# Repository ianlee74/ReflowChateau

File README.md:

# Reflow Chateau
The Reflow Chateau is a set of mods created by Will Floyd-Jones to convert a toaster oven to a reflow oven.  These are my mods/improvements to his original design.

The original Reflow Chateau project can be found here:
http://www.willfj.com/reflow-chateau/

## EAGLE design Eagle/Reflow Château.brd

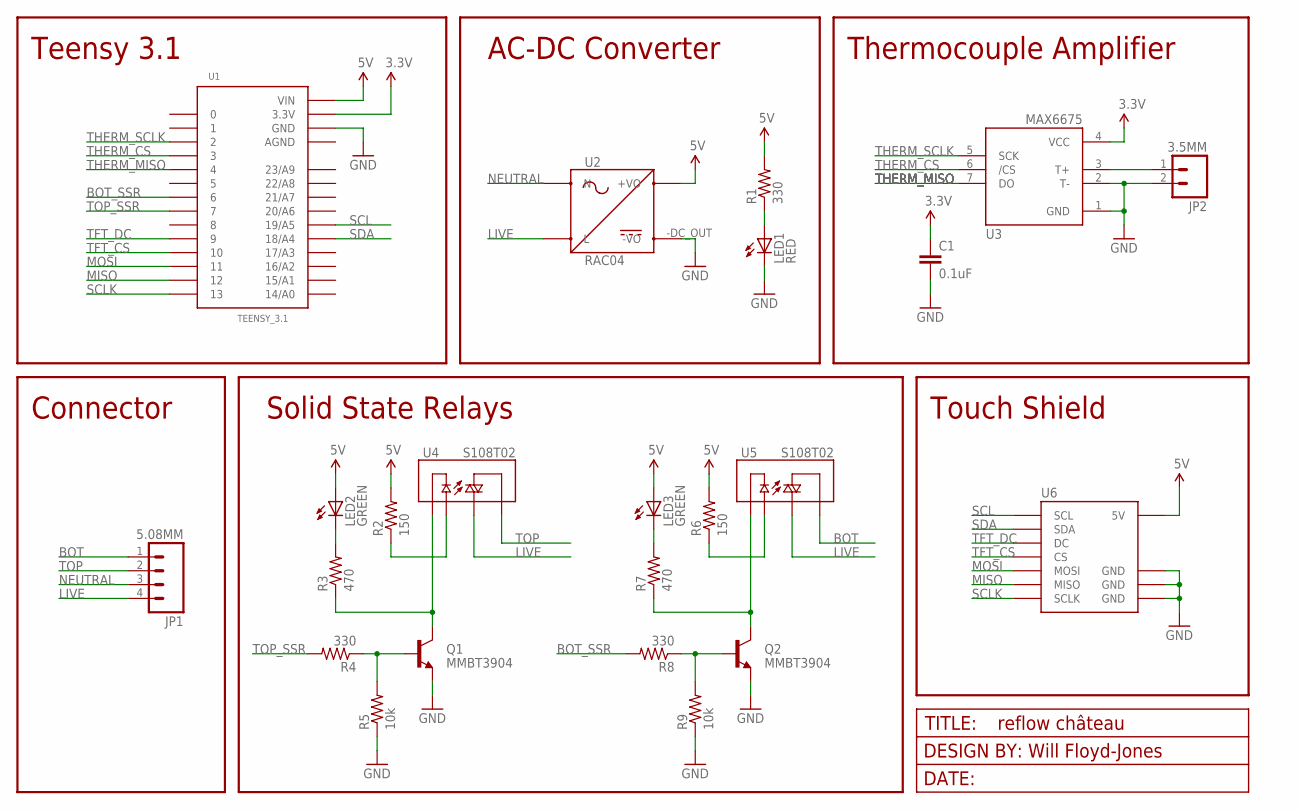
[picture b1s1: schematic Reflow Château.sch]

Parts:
C1: 0.1uF; 0603-CAP
JP1: 5.08MM; SCREWTERMINAL-5.08MM-4
JP2: 3.5MM; SCREWTERMINAL-3.5MM-2_LOCK
LED1: RED; LED-1206
LED2, LED3: GREEN; LED-1206
Q1, Q2: MMBT3904; SOT23-3
R1, R4, R8: 330; 0603-RES
R2, R6: 150; 0603-RES
R3, R7: 470; 0603-RES
R5, R9: 10k; 0603-RES
U1: TEENSY_3.1
U2: RAC04
U3: MAX6675; SO08
U4, U5: S108T02; RELAY-S108T02
U6: CAPACITIVE_TOUCH
U$9: FRAME; F-J_LOGO

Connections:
3.3V: C1.1, U1.3.3V, U3.4 (VCC)
5V: LED2.A, LED3.A, R1.2, R2.2, R6.2, U1.VIN, U2.+DC_OUT (+VO), U6.5V
AGND: U1.AGND
BOT: JP1.1, U5.1 (T1)
BOT_SSR: R8.2, U1.6
COIL: Q1.3 (C), R3.1, U4.4 (-)
COIL1: Q2.3 (C), R7.1, U5.4 (-)
GND: C1.2, JP2.2, LED1.C, Q1.2 (E), Q2.2 (E), R5.1, R9.1, U1.GND, U2.-DC_OUT (-VO), U3.1 (GND), U3.2 (T-), U6.GND, U6.GND@1 (GND), U6.GND@2 (GND)
LIVE: JP1.4, U2.LIVE (L), U4.2 (T2), U5.2 (T2)
MISO: U1.12, U6.D12 (MISO)
MOSI: U1.11, U6.D11 (MOSI)
unnamed: JP2.1, U3.3 (T+)
unnamed: R2.1, U4.3 (+)
unnamed: Q2.1 (B), R8.1, R9.2
unnamed: Q1.1 (B), R4.1, R5.2
unnamed: LED1.A, R1.1
unnamed: LED3.C, R7.2
unnamed: LED2.C, R3.2
unnamed: R6.1, U5.3 (+)
NEUTRAL: JP1.3, U2.NEUTRAL (N)
SCL: U1.19/A5, U6.SCL
SCLK: U1.13, U6.D13 (SCLK)
SDA: U1.18/A4, U6.SDA
TFT_CS: U1.10, U6.D10 (CS)
TFT_DC: U1.9, U6.D9 (DC)
THERM_CS: U1.3, U3.6 (/CS)
THERM_MISO: U1.4, U3.7 (DO)
THERM_SCLK: U1.2, U3.5 (SCK)
TOP: JP1.2, U4.1 (T1)
TOP_SSR: R4.2, U1.7

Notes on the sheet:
AC-DC Converter
Thermocouple Amplifier
Solid State Relays
Touch Shield
Connector
Teensy 3.1

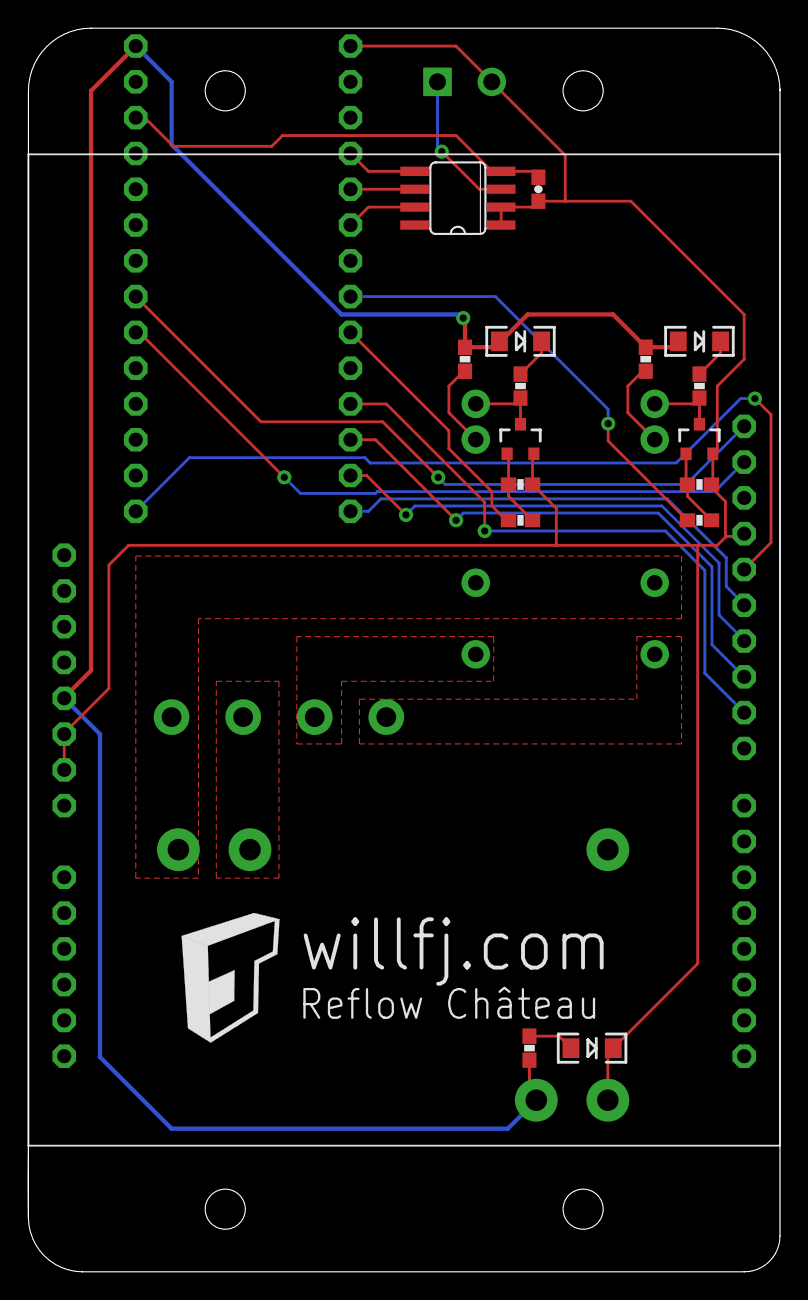
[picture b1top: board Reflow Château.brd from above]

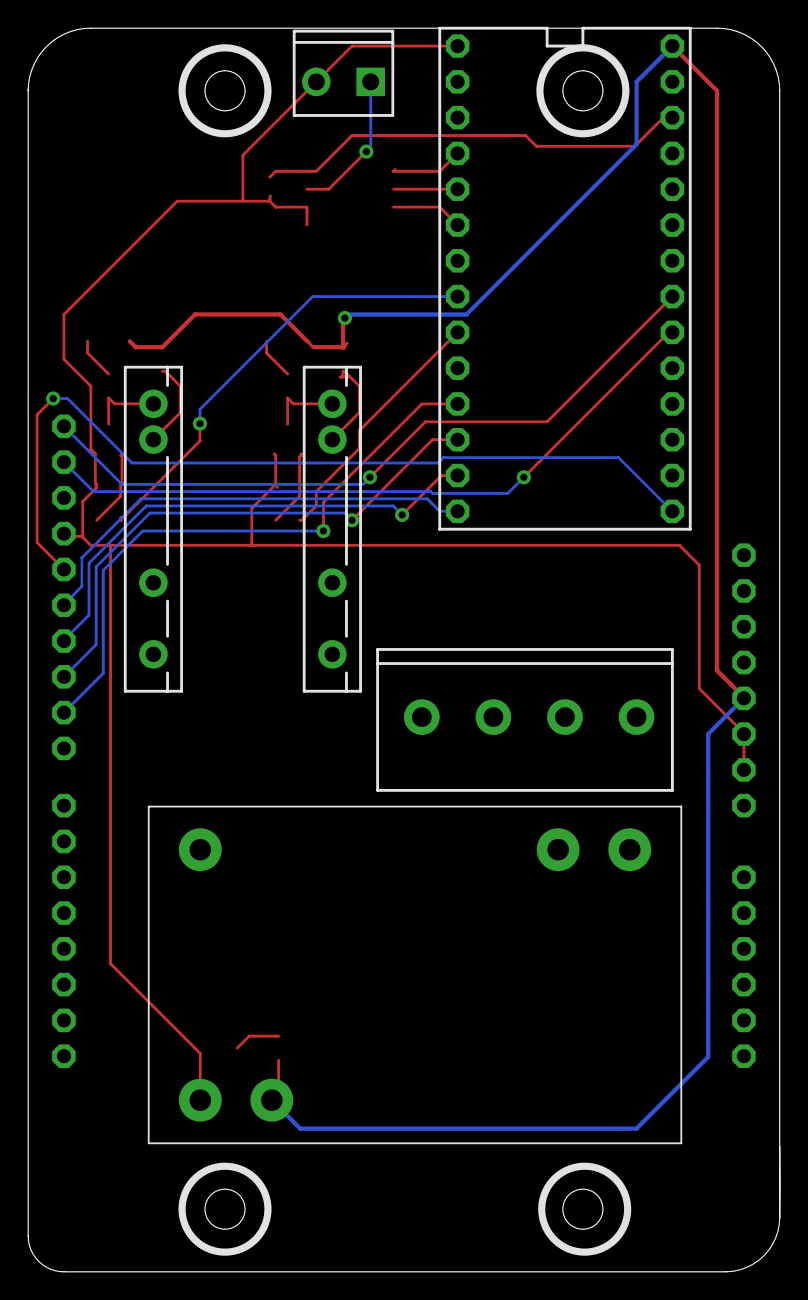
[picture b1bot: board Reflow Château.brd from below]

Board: 2 copper layers, 53.4 x 88.3 mm, 24 parts (6 on the bottom side), 29 nets.

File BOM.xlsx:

Device | Package | Part Number(s) | Quantity | Vendor | Vendor Pin | Unit Price | Ext Price
MAX6675 | SO08 | U3 | 1 | Digikey | MAX6675ISA+TCT-ND | 14.33 | 14.33
S108T02 SSR | 4-SIP | U4, U5 | 2 | Digikey | 425-2396-5-ND | 5.0999999999999996 | 10.199999999999999
Screw Terminal | 3.50 mm pitch | JP2 | 1 | Digikey | ED1514-ND | 0.68 | 0.68
Screw Terminal | 5.08 mm pitch | JP1 | 1 | Digikey | 281-1437-ND | 2.04 | 2.04
0.8 A, 5V AC-DC Converter | Through hole | U2 | 1 | Digikey | 945-2164-5-ND | 15.02 | 15.02
Teensy female headers | 14 position 0.1" | U1 | 2 | Digikey | S7047-ND | 1.18 | 2.36
Touchscreen female headers | 6 position 0.1" | U6 | 1 | Digikey | S7039-ND | 0.7 | 0.7
Touchscreen female headers | 8 position 0.1" | U6 | 2 | Digikey | S7043-ND | 0.84 | 1.68
Touchscreen female headers | 10 position 0.1" | U6 | 1 | Digikey | S7041-ND | 0.89 | 0.89
150 Ω Resistor | 0603 | R2, R6 | 25 | Digikey | 311-150GRCT-ND | 7.1999999999999998E-3 | 0.18
330 Ω Resistor | 0603 | R1, R4, R8 | 25 | Digikey | 311-330GRCT-ND | 7.1999999999999998E-3 | 0.18
470 Ω Resistor | 0603 | R3, R7 | 25 | Digikey | 311-470GRCT-ND | 7.1999999999999998E-3 | 0.18
10k Ω Resistor | 0603 | R5, R9 | 25 | Digikey | 311-10KGRCT-ND | 7.1999999999999998E-3 | 0.18
0.1 uF Capacitor | 0603 | C1 | 10 | Digikey | 490-1532-1-ND | 1.9E-2 | 0.19
MMBT3904 | SOT23-3 | Q1, Q2 | 2 | Digikey | MMBT3904TPMSCT-ND | 0.14000000000000001 | 0.28000000000000003
Red LED | 1206 | LED1 | 1 | Digikey | 1516-1076-1-ND | 0.52 | 0.52
Green LED | 1206 | LED2, LED3 | 2 | Digikey | 1516-1073-1-ND | 0.47 | 0.94
Teensy 3.1 | NA | U1 | 1 | Adafruit | 1625 | 19.95 | 19.95
K-Type Thermocouple | NA | NA | 1 | Adafruit | 270 | 9.9499999999999993 | 9.9499999999999993
Capacitive Touchscreen | Arduino shield | U6 | 1 | Adafruit | 1947 | 44.95 | 44.95
Digital Toaster | NA | NA | 1 | Sears | 00829294000P | 49.99 | 49.99
3/8" 4-40 Machine Screw | NA | NA | 1 | Digikey | H781-ND | 2.46E-2 | 2.46E-2 |  | * Min qty 100
PCB (2 layer, 10cm x 10cm) |  |  | 1 | DFRobot | http://www.dfrobot.com/index.php?route=product/product&path=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 | 5 | 5
 |  |  |  |  |  | TOTAL | 180.41460000000001 |  | * Shipping not included

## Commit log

2015-04-19 Original files from Will-Floyd.
2015-04-19 Updated the readme.
2015-04-20 Rotated plate for easy printing without rotating in printing software. Added 'Power' text.
2015-04-21 Added LCD border cover and backlit text.
2015-04-21 Increased size of text and increased thickness between text and front.
2015-04-21 Added .7mm tolerance around the display to ease assembly.
2015-04-23 Increased thickness of LCD frame.
2015-04-25 Increased font size of text.
2016-09-25 Create Adafruit_FT6206.cpp
    This is one of the two necessary files for compilation that are not included in the original code.
2016-09-25 Create Adafruit_FT6206.h
    This is one of the two necessary files for compilation that are not included in the original code.

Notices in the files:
parts and their libraries:
SparkFun-Resistors: Licensing: Creative Commons ShareAlike 4.0 International - https://creativecommons.org/licenses/by-sa/4.0
